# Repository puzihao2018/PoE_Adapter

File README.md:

# PoE_Adapter

## The Idea

## Requirements

* Support 802.3af, at, bt
* Maximum PoE input 71W
* Support 10M/100M/1G Ethernet, 2.5G or 10G better
* Support USB PD 60W(20V-3A) or higher, max to 65W
* Support USB PD 2.0 or higher, PPS support is better

## Related Knowledge

### About PoE

[什么是Power over Ethernet（PoE）? 它是如何工作的？ - 华为](https://info.support.huawei.com/info-finder/encyclopedia/zh/PoE.html)

[Power over Ethernet - Wikipedia](https://en.wikipedia.org/wiki/Power_over_Ethernet)

[【全系列】电源大咖课终极篇：EMC/功率隔离/PoE/LTspice_哔哩哔哩_bilibili](https://www.bilibili.com/video/BV1U54y167iA?p=6&vd_source=4a5614e8aaa017dad2b9a475db5972fe)

### About DCDC

### About USB2ETH

## Key Components

* [ ] 网口变压器
* [ ] PoE Interface IC
* [ ] ETH PHY Chip, MDI/MDIX to SGMII
* [ ] DCDC
* [ ] PD Control IC
* [ ] USB2ETH IC

## Possible Test Equipments

### PSE Devices

[HUAWEI ****AD-560161T0E POE++ Injector****](https://www.notion.so/HUAWEI-AD-560161T0E-POE-Injector-f2f963361bf641c6bf67e5bd52b6a7db)

[**Cudy POE400 90W Gigabit Ultra PoE++ Injector Adapter**](https://www.notion.so/Cudy-POE400-90W-Gigabit-Ultra-PoE-Injector-Adapter-ba70eb35d22a4e3bbaf1a9ec274cac1c)

[H3C S5130S-10MS-UPWR-EI Switch](https://www.notion.so/H3C-S5130S-10MS-UPWR-EI-Switch-632d7c23edca47faa28a7068c8aec5ac)

[QNAP ****QSW-M2116P-2T2S Switch****](https://www.notion.so/QNAP-QSW-M2116P-2T2S-Switch-efeddbc0777d48369dd353b2ddde7140)

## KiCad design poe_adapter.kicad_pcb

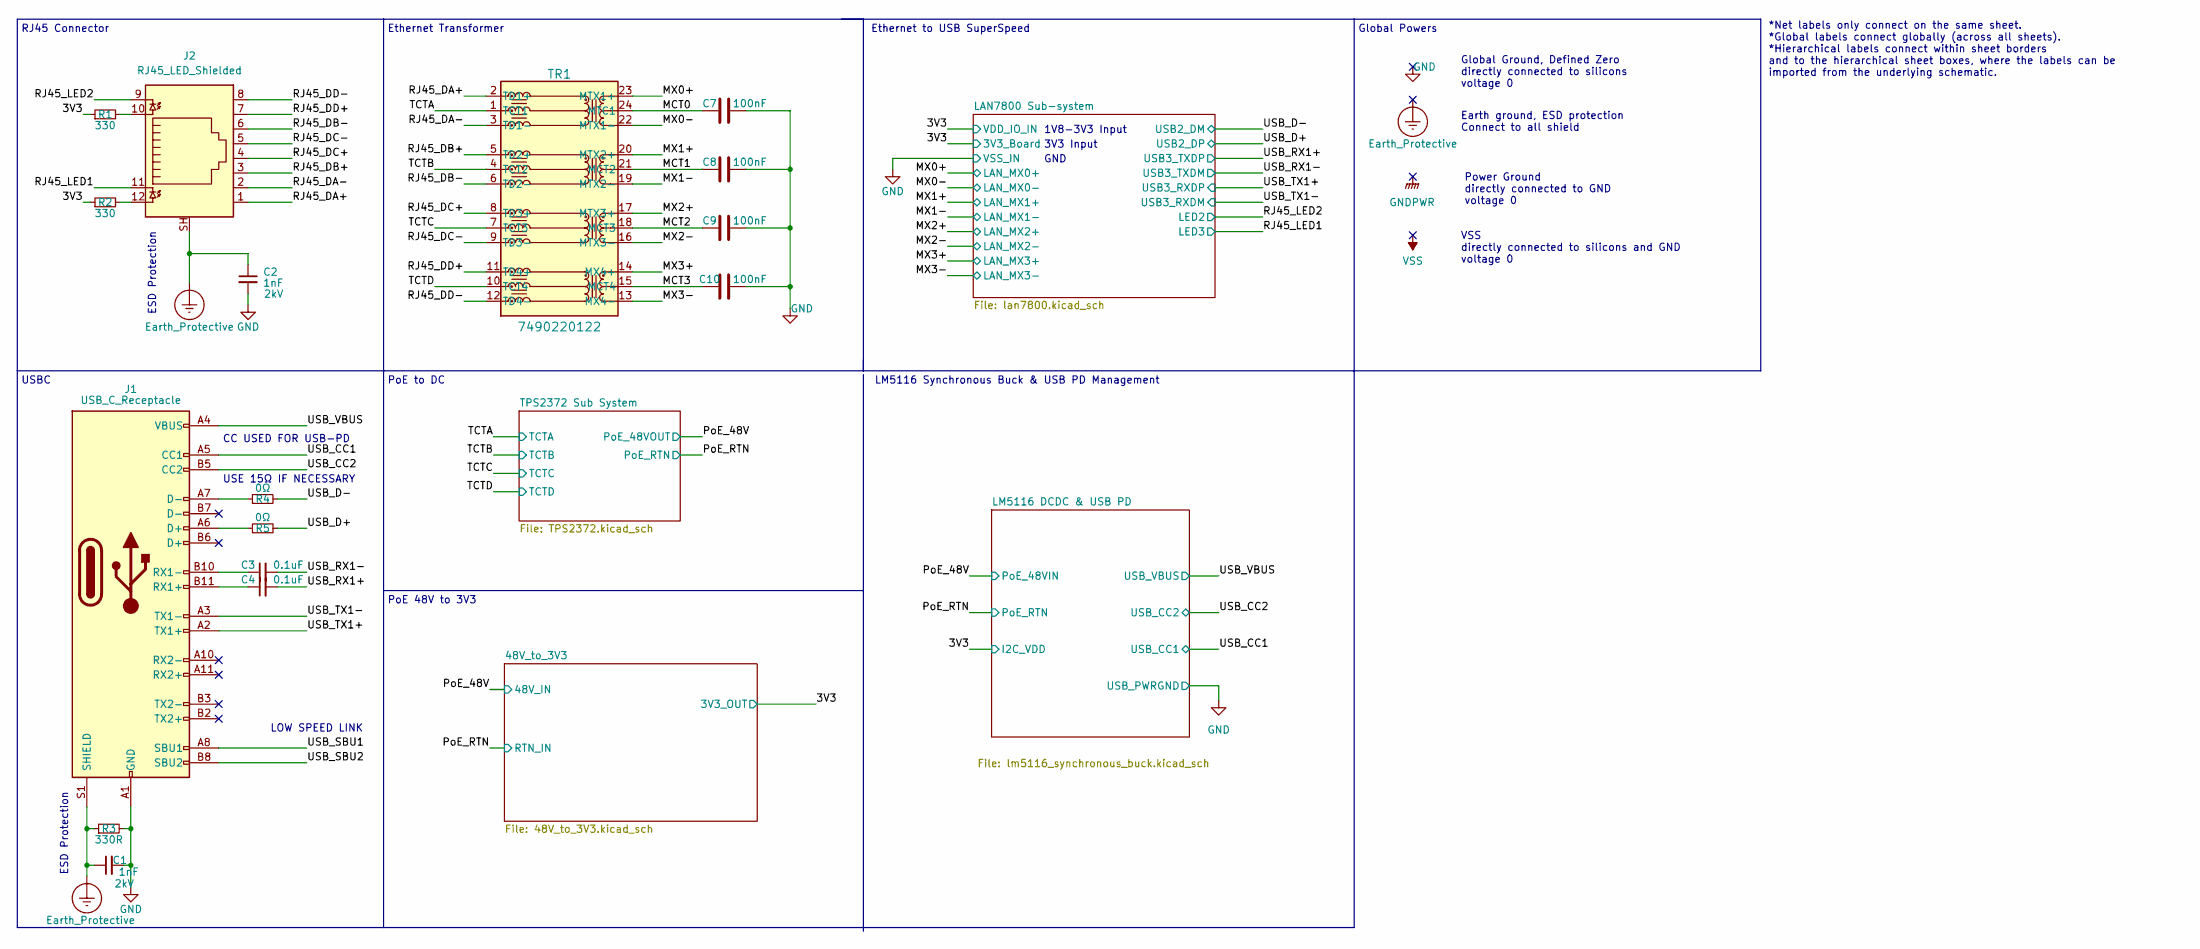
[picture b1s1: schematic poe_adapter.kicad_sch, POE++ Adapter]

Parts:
C1: 1nF; C_1206_3216Metric; Voltage 2kV
C2: 1nF; R_1206_3216Metric; Voltage 2kV
C3, C4: 0.1uF; C_0603_1608Metric
C7, C8, C9, C10: 100nF; C_1206_3216Metric
J1: USB_C_Receptacle; USB_C_Receptacle_Amphenol_12401610E4-2A_CircularHoles
J2: RJ45_LED_Shielded; RJ45_Amphenol_RJHSE538X
R1, R2: 330; R_0603_1608Metric
R3: 330R; R_0603_1608Metric
R4, R5: 0Ω; R_0603_1608Metric
TR1: 7490220122

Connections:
/MCT0: C7.2, TR1.24 (MTC1)
/MCT1: C8.2, TR1.21 (MCT2)
/MCT2: C9.2, TR1.18 (MCT3)
/MCT3: C10.2, TR1.15 (MCT4)
/MX0+: TR1.23 (MTX1+); also elsewhere on the board
/MX0-: TR1.22 (MTX1-); also elsewhere on the board
/MX1+: TR1.20 (MTX2+); also elsewhere on the board
/MX1-: TR1.19 (MTX2-); also elsewhere on the board
/MX2+: TR1.17 (MTX3+); also elsewhere on the board
/MX2-: TR1.16 (MTX3-); also elsewhere on the board
/MX3+: TR1.14 (MX4+); also elsewhere on the board
/MX3-: TR1.13 (MX4-); also elsewhere on the board
/RJ45_DA+: J2.1, TR1.2 (TD1+)
/RJ45_DA-: J2.2, TR1.3 (TD1-)
/RJ45_DB+: J2.3, TR1.5 (TD2+)
/RJ45_DB-: J2.6, TR1.6 (TD2-)
/RJ45_DC+: J2.4, TR1.8 (TD3+)
/RJ45_DC-: J2.5, TR1.9 (TD3-)
/RJ45_DD+: J2.7, TR1.11 (TD4+)
/RJ45_DD-: J2.8, TR1.12 (TD4-)
/RJ45_LED1: J2.11; also elsewhere on the board
/RJ45_LED2: J2.9; also elsewhere on the board
/TCTA: TR1.1 (TCT1); also elsewhere on the board
/TCTB: TR1.4 (TCT2); also elsewhere on the board
/TCTC: TR1.7 (TCT3); also elsewhere on the board
/TCTD: TR1.10 (TCT4); also elsewhere on the board
/USB_CC1: J1.A5 (CC1); also elsewhere on the board
/USB_CC2: J1.B5 (CC2); also elsewhere on the board
/USB_D+: R5.2; also elsewhere on the board
/USB_D-: R4.2; also elsewhere on the board
/USB_RX1+: C4.2; also elsewhere on the board
/USB_RX1-: C3.2; also elsewhere on the board
/USB_SBU1: J1.A8 (SBU1)
/USB_SBU2: J1.B8 (SBU2)
/USB_TX1+: J1.A2 (TX1+); also elsewhere on the board
/USB_TX1-: J1.A3 (TX1-); also elsewhere on the board
/USB_VBUS: J1.A4 (VBUS), J1.A9 (VBUS), J1.B4 (VBUS), J1.B9 (VBUS); also elsewhere on the board
Earth_Protective: C1.1, C2.1, J1.S1 (SHIELD), J2.SH, R3.1; also elsewhere on the board
unnamed: C3.1, J1.B10 (RX1-)
unnamed: C4.1, J1.B11 (RX1+)
unnamed: J1.A6 (D+), R5.1
unnamed: J1.A7 (D-), R4.1
unnamed: J2.10, R1.2
unnamed: J2.12, R2.2

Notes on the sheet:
USE 15Ω IF NECESSARY
RJ45 Connector
1V8-3V3 Input
Ethernet to USB SuperSpeed
Ethernet Transformer
PoE to DC
Earth ground, ESD protection Connect to all shield
Global Ground, Defined Zero directly connected to silicons voltage 0
USBC
GND
3V3 Input
CC USED FOR USB-PD
ESD Protection
LOW SPEED LINK
Power Ground directly connected to GND voltage 0
*Net labels only connect on the same sheet. *Global labels connect globally (across all sheets). *Hierarchical labels connect within sheet borders and to the hierarchical sheet boxes, where the labels can be imported from the underlying schematic.
VSS directly connected to silicons and GND voltage 0
PoE 48V to 3V3
LM5116 Synchronous Buck & USB PD Management
Global Powers

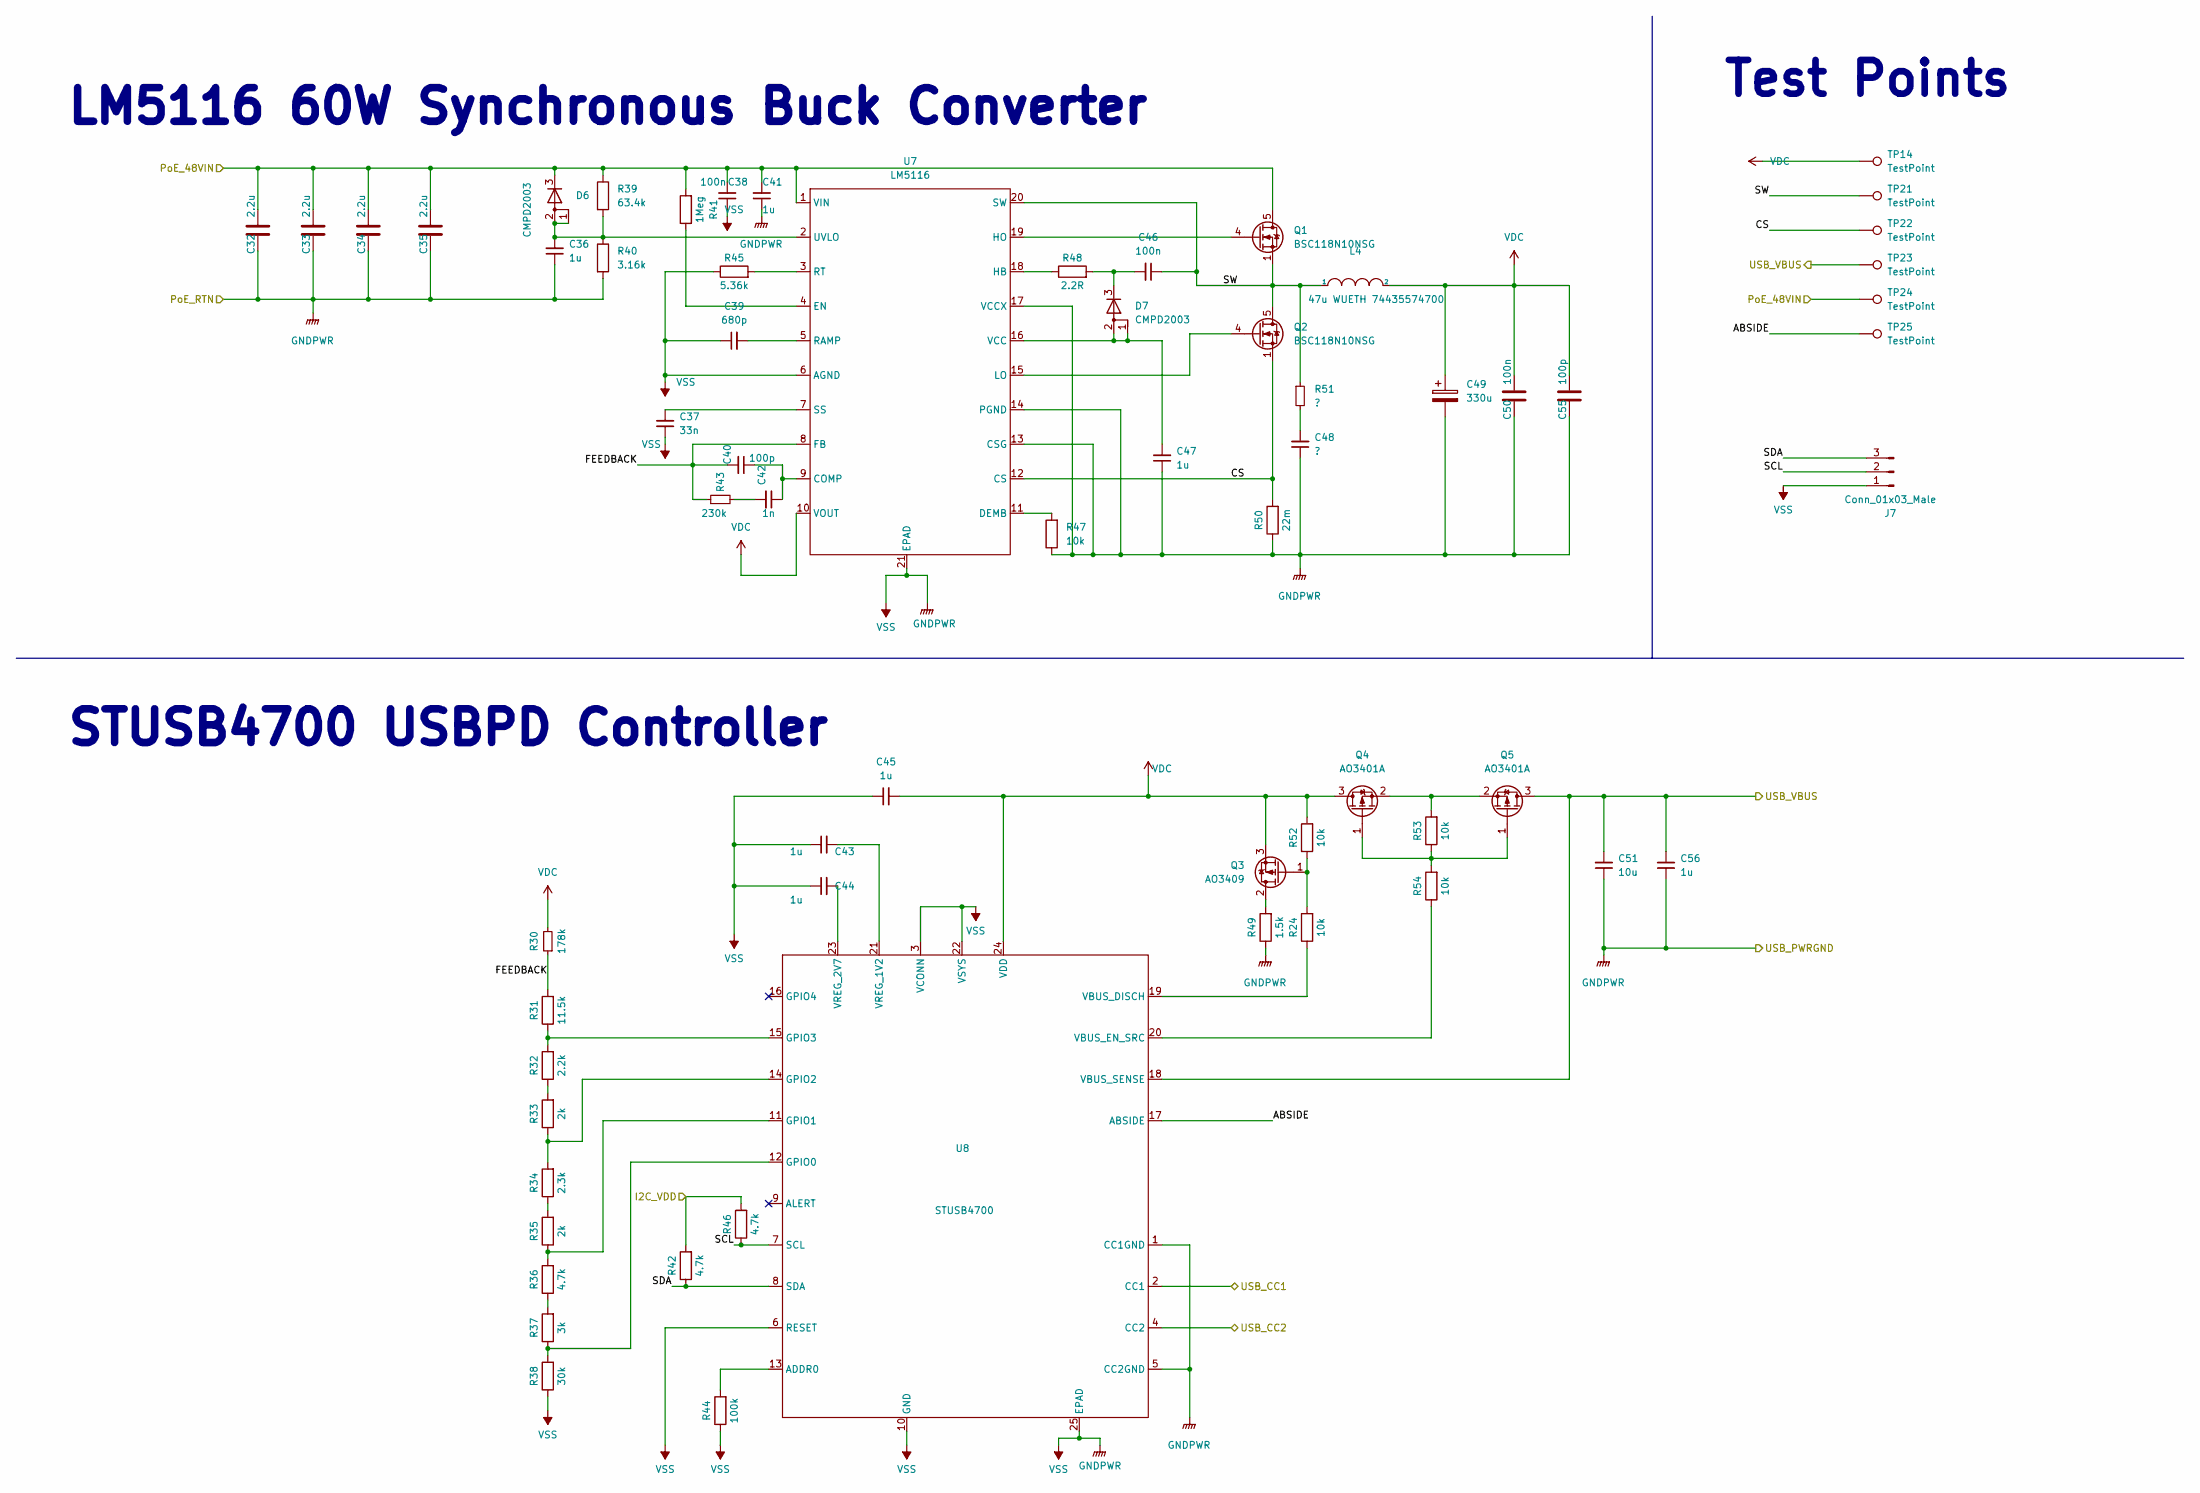
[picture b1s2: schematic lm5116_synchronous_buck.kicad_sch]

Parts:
C32, C33, C34, C35: 2.2u; C_0603_1608Metric
C36, C41, C43, C44, C45, C47, C56: 1u; C_0603_1608Metric
C37: 33n; C_0603_1608Metric
C38, C46, C50: 100n; C_0603_1608Metric
C39: 680p; C_0603_1608Metric
C40, C55: 100p; C_0603_1608Metric
C42: 1n; C_0603_1608Metric
C48: ?; C_0603_1608Metric
C49: 330u; C_Elec_10x10.2
C51: 10u; C_0805_2012Metric
D6, D7: CMPD2003; SOT-23
J7: Conn_01x03_Male; PinHeader_1x03_P1.00mm_Vertical
L4: 47u WUETH 74435574700; 74435574700
Q1, Q2: BSC118N10NSG; TDSON-8-1
Q3: AO3409; SOT-23
Q4, Q5: AO3401A; SOT-23
R24, R47, R52, R53, R54: 10k; R_0603_1608Metric
R30: 178k; R_0603_1608Metric
R31: 11.5k; R_0603_1608Metric
R32: 2.2k; R_0603_1608Metric
R33, R35: 2k; R_0603_1608Metric
R34: 2.3k; R_0603_1608Metric
R36, R42, R46: 4.7k; R_0603_1608Metric
R37: 3k; R_0603_1608Metric
R38: 30k; R_0603_1608Metric
R39: 63.4k; R_0603_1608Metric
R40: 3.16k; R_0603_1608Metric
R41: 1Meg; R_0603_1608Metric
R43: 230k; R_0603_1608Metric
R44: 100k; R_0603_1608Metric
R45: 5.36k; R_0603_1608Metric
R48: 2.2R; R_0805_2012Metric
R49: 1.5k; R_0603_1608Metric
R50: 22m; R_1206_3216Metric
R51: ?; R_0603_1608Metric
TP14, TP21, TP22, TP23, TP24, TP25: TestPoint; TestPoint_Pad_1.0x1.0mm
U7: LM5116; HTSSOP-20-1EP_4.4x6.5mm_P0.65mm_EP2.85x4mm
U8: STUSB4700; QFN-24-1EP_4x4mm_P0.5mm_EP2.7x2.7mm_ThermalVias

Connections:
/LM5116 DCDC & USB PD/ABSIDE: TP25.1, U8.17 (ABSIDE)
/LM5116 DCDC & USB PD/CS: Q2.1 (S), Q2.2 (S), Q2.3 (S), R50.2, TP22.1, U7.12 (CS)
/LM5116 DCDC & USB PD/FEEDBACK: C40.2, R30.1, R31.2, R43.1, U7.8 (FB)
/LM5116 DCDC & USB PD/SCL: J7.2, R46.1, U8.7 (SCL)
/LM5116 DCDC & USB PD/SDA: J7.3, R42.1, U8.8 (SDA)
/LM5116 DCDC & USB PD/SW: C46.1, L4.1, Q1.1 (S), Q1.2 (S), Q1.3 (S), Q2.5 (D), R51.1, TP21.1, U7.20 (SW)
/PoE_48V: C32.1, C33.1, C34.1, C35.1, C38.2, C41.2, D6.3 (K), Q1.5 (D), R39.1, R41.2, TP24.1, U7.1 (VIN); also elsewhere on the board
/USB_CC1: U8.2 (CC1); also elsewhere on the board
/USB_CC2: U8.4 (CC2); also elsewhere on the board
/USB_VBUS: C51.2, C56.2, Q5.3 (D), TP23.1, U8.18 (VBUS_SENSE); also elsewhere on the board
unnamed: C36.2, D6.1 (A), D6.2 (A), R39.2, R40.1, U7.2 (UVLO)
unnamed: C37.2, U7.7 (SS)
unnamed: C39.2, U7.5 (RAMP)
unnamed: C40.1, C42.1, U7.9 (COMP)
unnamed: C42.2, R43.2
unnamed: C43.2, U8.21 (VREG_1V2)
unnamed: C44.2, U8.23 (VREG_2V7)
unnamed: C46.2, D7.3 (K), R48.2
unnamed: C47.2, D7.1 (A), D7.2 (A), U7.16 (VCC)
unnamed: C48.2, R51.2
unnamed: Q1.4 (G), U7.19 (HO)
unnamed: Q2.4 (G), U7.15 (LO)
unnamed: Q3.1 (G), R24.2, R52.1
unnamed: Q3.2 (D), R49.2
unnamed: Q4.1 (G), Q5.1 (G), R53.1, R54.2
unnamed: Q4.2 (S), Q5.2 (S), R53.2
unnamed: R24.1, U8.19 (VBUS_DISCH)
unnamed: R31.1, R32.2, U8.15 (GPIO3)
unnamed: R32.1, R33.2
unnamed: R33.1, R34.2, U8.14 (GPIO2)
unnamed: R34.1, R35.2
unnamed: R35.1, R36.2, U8.11 (GPIO1)
unnamed: R36.1, R37.2
unnamed: R37.1, R38.2, U8.12 (GPIO0)
unnamed: R41.1, U7.4 (EN)
unnamed: R44.2, U8.13 (ADDR0)
unnamed: R45.2, U7.3 (RT)
unnamed: R47.2, U7.11 (DEMB)
unnamed: R48.1, U7.18 (HB)
unnamed: R54.1, U8.20 (VBUS_EN_SRC)
VDC: C45.2, C49.1, C50.1, C55.1, L4.2, Q3.3 (S), Q4.3 (D), R30.2, R52.2, TP14.1, U7.10 (VOUT), U8.24 (VDD)

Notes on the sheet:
STUSB4700 USBPD Controller
Test Points
LM5116 60W Synchronous Buck Converter

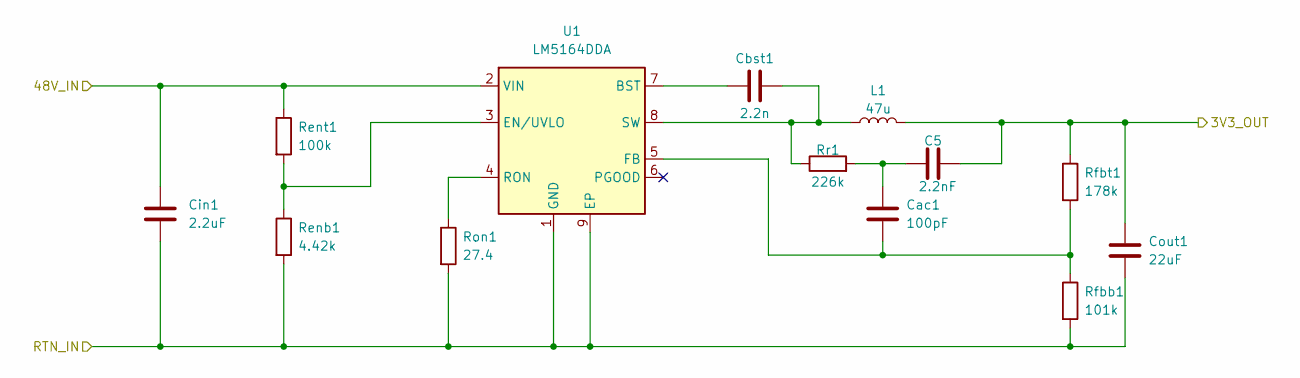
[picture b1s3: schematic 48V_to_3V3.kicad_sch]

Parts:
C5: 2.2nF; C_0603_1608Metric
Cac1: 100pF; C_0603_1608Metric
Cbst1: 2.2n; C_0603_1608Metric
Cin1: 2.2uF; C_1206_3216Metric
Cout1: 22uF; C_1206_3216Metric
L1: 47u; L_Wuerth_HCI-5040
Renb1: 4.42k; R_0603_1608Metric
Rent1: 100k; R_0603_1608Metric
Rfbb1: 101k; R_0603_1608Metric
Rfbt1: 178k; R_0603_1608Metric
Ron1: 27.4; R_0603_1608Metric
Rr1: 226k; R_0603_1608Metric
U1: LM5164DDA; HSOP-8-1EP_3.9x4.9mm_P1.27mm_EP2.41x3.1mm_ThermalVias

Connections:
/PoE_48V: C5.1, Cac1.2, Cin1.2, Cout1.1, Renb1.2, Rfbb1.2, Ron1.2, Rr1.2, U1.1 (VIN), U1.9 (EP); also elsewhere on the board
unnamed: Cbst1.1, U1.7 (BST)
unnamed 96: Ron1.1, U1.4 (FB); also elsewhere on the board

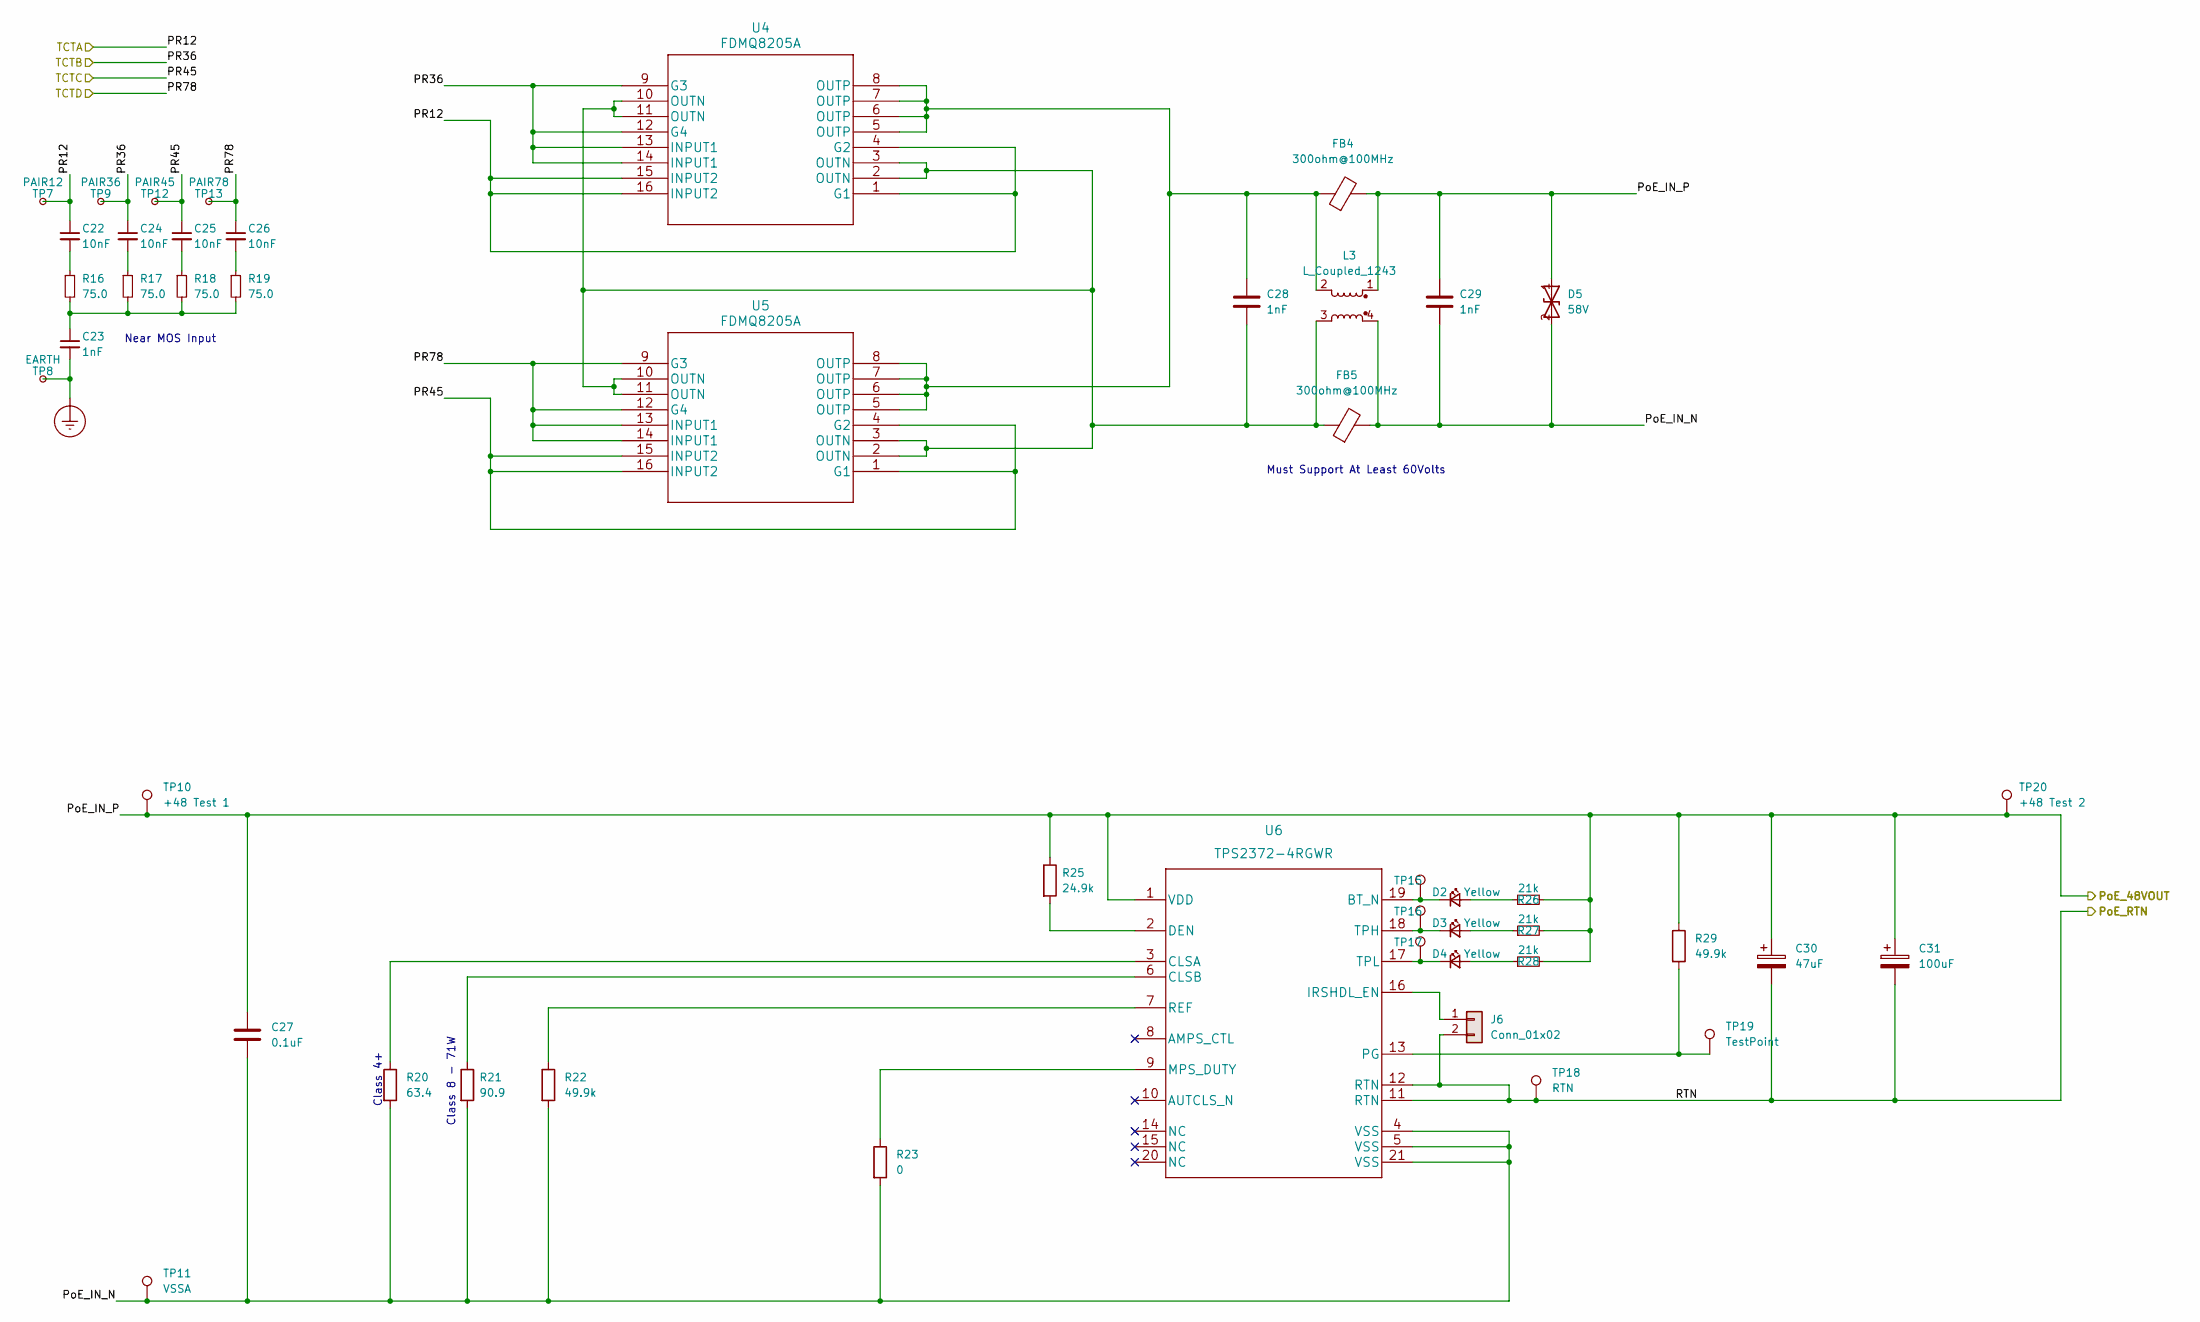
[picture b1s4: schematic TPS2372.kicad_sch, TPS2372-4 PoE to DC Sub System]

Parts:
C22, C24, C25, C26: 10nF; C_0603_1608Metric
C23, C28, C29: 1nF; C_0603_1608Metric
C27: 0.1uF; C_0805_2012Metric
C30: 47uF; EEV-TG2A470Q
C31: 100uF; CP_Elec_16x17.5
D2, D3, D4: Yellow; D_0603_1608Metric
D5: 58V; D_SMB
FB4, FB5: 300ohm@100MHz; L_0603_1608Metric
J6: Conn_01x02; PinHeader_1x02_P2.54mm_Vertical
L3: L_Coupled_1243; 744272251
R16, R17, R18, R19: 75.0; R_0603_1608Metric
R20: 63.4; R_0201_0603Metric
R21: 90.9; R_0603_1608Metric
R22, R29: 49.9k; R_0603_1608Metric
R23: 0; R_0603_1608Metric
R25: 24.9k; R_0603_1608Metric
R26, R27, R28: 21k; R_0603_1608Metric
TP7: PAIR12; TestPoint_Pad_1.0x1.0mm
TP8: EARTH; TestPoint_Pad_1.0x1.0mm
TP9: PAIR36; TestPoint_Pad_1.0x1.0mm
TP10: +48 Test 1; TestPoint_Pad_1.0x1.0mm
TP11: VSSA; TestPoint_Pad_1.0x1.0mm
TP12: PAIR45; TestPoint_Pad_1.0x1.0mm
TP13: PAIR78; TestPoint_Pad_1.0x1.0mm
TP15, TP16, TP17, TP19: TestPoint; TestPoint_Pad_1.0x1.0mm
TP18: RTN; TestPoint_Pad_1.0x1.0mm
TP20: +48 Test 2; TestPoint_Pad_1.0x1.0mm
U4, U5: FDMQ8205A
U6: TPS2372-4RGWR; TPS2372-3RGWR

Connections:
/PoE_48V: C27.1, C29.1, C30.1, C31.1, D5.1 (A1), FB4.2, L3.1, R25.1, R26.2, R27.2, R28.2, R29.1, TP10.1, TP20.1, U6.1 (VDD); also elsewhere on the board
/TCTA: C22.1, TP7.1, U4.1 (G1), U4.4 (G2), U4.15 (INPUT2), U4.16 (INPUT2); also elsewhere on the board
/TCTB: C24.1, TP9.1, U4.9 (G3), U4.12 (G4), U4.13 (INPUT1), U4.14 (INPUT1); also elsewhere on the board
/TCTC: C25.1, TP12.1, U5.1 (G1), U5.4 (G2), U5.15 (INPUT2), U5.16 (INPUT2); also elsewhere on the board
/TCTD: C26.1, TP13.1, U5.9 (G3), U5.12 (G4), U5.13 (INPUT1), U5.14 (INPUT1); also elsewhere on the board
/TPS2372 Sub System/PoE_IN_N: C27.2, C29.2, D5.2 (A2), FB5.2, L3.4, R20.2, R21.2, R22.2, R23.2, TP11.1, U6.4 (VSS), U6.5 (VSS), U6.21 (VSS)
Earth_Protective: C23.2, TP8.1; also elsewhere on the board
unnamed: C22.2, R16.1
unnamed: C23.1, R16.2, R17.2, R18.2, R19.2
unnamed: C24.2, R17.1
unnamed: C25.2, R18.1
unnamed: C26.2, R19.1
unnamed: C28.1, FB4.1, L3.2, U4.5 (OUTP), U4.6 (OUTP), U4.7 (OUTP), U4.8 (OUTP), U5.5 (OUTP), U5.6 (OUTP), U5.7 (OUTP), U5.8 (OUTP)
unnamed: C28.2, FB5.1, L3.3, U4.2 (OUTN), U4.3 (OUTN), U4.10 (OUTN), U4.11 (OUTN), U5.2 (OUTN), U5.3 (OUTN), U5.10 (OUTN), U5.11 (OUTN)
unnamed: D2.1 (K), TP15.1, U6.19 (BT_N)
unnamed: D2.2 (A), R26.1
unnamed: D3.1 (K), TP16.1, U6.18 (TPH)
unnamed: D3.2 (A), R27.1
unnamed: D4.1 (K), TP17.1, U6.17 (TPL)
unnamed: D4.2 (A), R28.1
unnamed: J6.1, U6.16 (IRSHDL_EN)
unnamed: R20.1, U6.3 (CLSA)
unnamed: R21.1, U6.6 (CLSB)
unnamed: R22.1, U6.7 (REF)
unnamed: R23.1, U6.9 (MPS_DUTY)
unnamed: R25.2, U6.2 (DEN)
unnamed: R29.2, TP19.1, U6.13 (PG)

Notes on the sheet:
Class 8 - 71W
Near MOS Input
Class 4+
Must Support At Least 60Volts

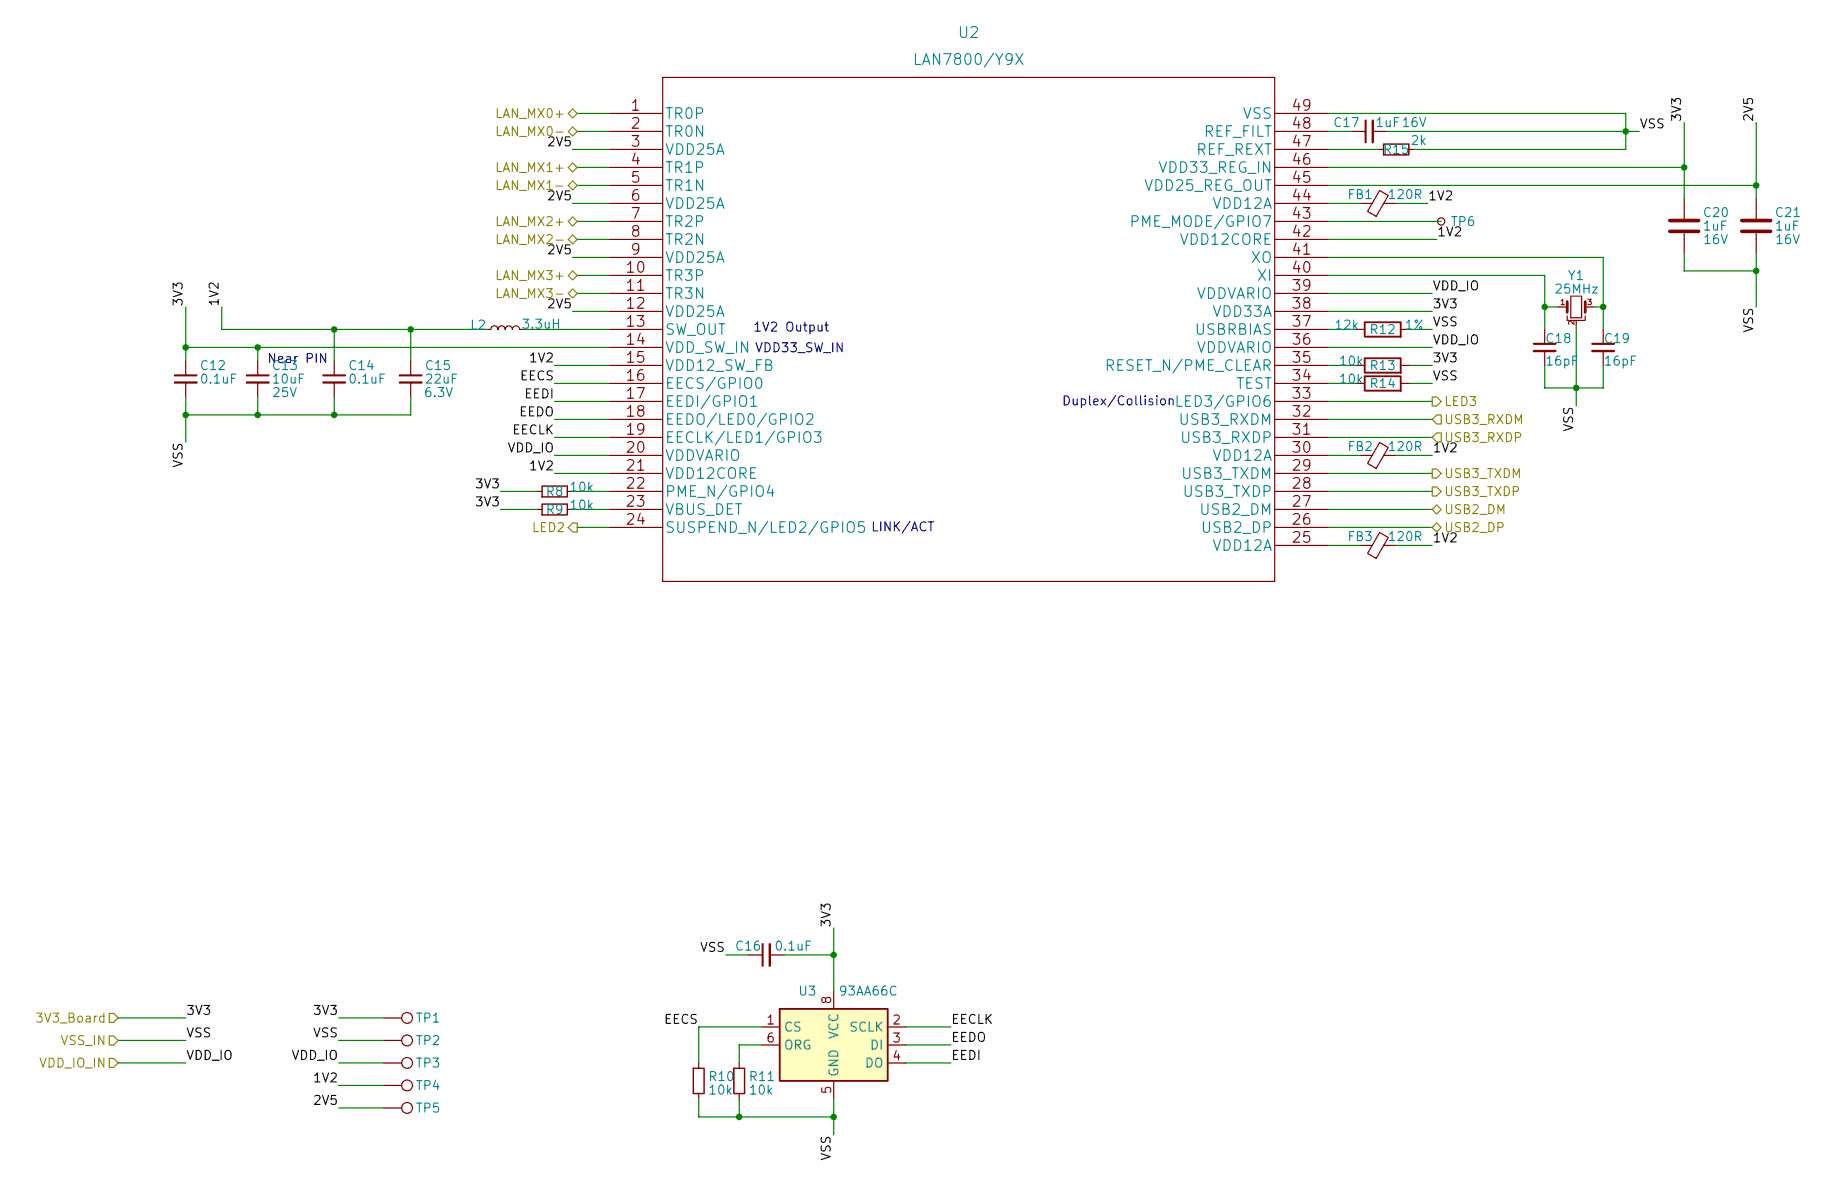
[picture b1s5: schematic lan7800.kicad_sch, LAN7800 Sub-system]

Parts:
C12, C14, C16: 0.1uF; C_0603_1608Metric
C13: 10uF; C_0603_1608Metric; Voltage 25V
C15: 22uF; C_0603_1608Metric; Voltage 6.3V
C17, C20, C21: 1uF; C_0603_1608Metric; Voltage 16V
C18, C19: 16pF; C_0603_1608Metric
FB1: 120R; L_0603_1608Metric
FB2, FB3: 120R; R_0603_1608Metric
L2: 3.3uH; L_1206_3216Metric
R8, R9, R10, R11, R13, R14: 10k; R_0603_1608Metric
R12: 12k; R_0603_1608Metric
R15: 2k; R_0603_1608Metric
TP1, TP2, TP3, TP4, TP5: TestPoint; TestPoint_Pad_1.0x1.0mm
TP6: TestPoint_Small; TestPoint_Pad_1.0x1.0mm
U2: LAN7800/Y9X; LAN7800&slash_Y9X
U3: 93AA66C; SOIC-8-1EP_3.9x4.9mm_P1.27mm_EP2.29x3mm
Y1: 25MHz; Crystal_SMD_3225-4Pin_3.2x2.5mm

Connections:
/LAN7800 Sub-system/1V2: C14.1, C15.1, FB1.2, FB2.2, FB3.2, L2.1, TP4.1, U2.15 (VDD12_SW_FB), U2.21 (VDD12CORE), U2.42 (VDD12CORE)
/LAN7800 Sub-system/2V5: C21.1, TP5.1, U2.3 (VDD25A), U2.6 (VDD25A), U2.9 (VDD25A), U2.12 (VDD25A), U2.45 (VDD25_REG_OUT)
/LAN7800 Sub-system/EECLK: U2.19 (EECLK/LED1/GPIO3), U3.2 (SCLK)
/LAN7800 Sub-system/EECS: R10.1, U2.16 (EECS/GPIO0), U3.1 (CS)
/LAN7800 Sub-system/EEDI: U2.17 (EEDI/GPIO1), U3.4 (DO)
/LAN7800 Sub-system/EEDO: U2.18 (EEDO/LED0/GPIO2), U3.3 (DI)
/MX0+: U2.1 (TR0P); also elsewhere on the board
/MX0-: U2.2 (TR0N); also elsewhere on the board
/MX1+: U2.4 (TR1P); also elsewhere on the board
/MX1-: U2.5 (TR1N); also elsewhere on the board
/MX2+: U2.7 (TR2P); also elsewhere on the board
/MX2-: U2.8 (TR2N); also elsewhere on the board
/MX3+: U2.10 (TR3P); also elsewhere on the board
/MX3-: U2.11 (TR3N); also elsewhere on the board
/RJ45_LED1: U2.33 (LED3/GPIO6); also elsewhere on the board
/RJ45_LED2: U2.24 (SUSPEND_N/LED2/GPIO5); also elsewhere on the board
/USB_D+: U2.26 (USB2_DP); also elsewhere on the board
/USB_D-: U2.27 (USB2_DM); also elsewhere on the board
/USB_RX1+: U2.28 (USB3_TXDP); also elsewhere on the board
/USB_RX1-: U2.29 (USB3_TXDM); also elsewhere on the board
/USB_TX1+: U2.31 (USB3_RXDP); also elsewhere on the board
/USB_TX1-: U2.32 (USB3_RXDM); also elsewhere on the board
unnamed: C17.1, U2.48 (REF_FILT)
unnamed: C18.1, U2.40 (XI), Y1.1
unnamed: C19.1, U2.41 (XO), Y1.3
unnamed: FB1.1, U2.44 (VDD12A)
unnamed: FB2.1, U2.30 (VDD12A)
unnamed: FB3.1, U2.25 (VDD12A)
unnamed: L2.2, U2.13 (SW_OUT)
unnamed: R8.2, U2.22 (PME_N/GPIO4)
unnamed: R9.2, U2.23 (VBUS_DET)
unnamed: R11.1, U3.6 (ORG)
unnamed: R12.1, U2.37 (USBRBIAS)
unnamed: R13.1, U2.35 (RESET_N/PME_CLEAR)
unnamed: R14.1, U2.34 (TEST)
unnamed: R15.1, U2.47 (REF_REXT)
unnamed: TP6.1, U2.43 (PME_MODE/GPIO7)

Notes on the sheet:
LINK/ACT
VDD33_SW_IN
1V2 Output
Duplex/Collision
Near PIN

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
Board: 4 copper layers, 170 parts (0 on the bottom side), 126 nets, no tracks yet.

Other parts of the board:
C6, C52, C53: 4.7uF; C_1206_3216Metric
C11: 330uF; CP_Elec_8x10
C54: 100uF; CP_Elec_10x10
D1: 60V 1A; D_SMA
R6: 3.4k; R_0603_1608Metric
R7: 2k; R_0603_1608Metric

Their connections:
/PoE_48V: C6.1, C52.1, C53.1, C54.1; also elsewhere on the board
unnamed 96: R6.2, R7.1; also elsewhere on the board

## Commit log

2022-07-07 repo init with readme
2022-07-07 LAN7800 Update 220707
2022-07-07 LAN7800 Update 220707-2
2022-07-10 LAN7800 update 0710
2022-07-12 Added initial annotated DCDC ic components and power stage design caculations
2022-07-12 finish datalink
2022-07-12 led update
2022-07-13 *updated power converter design calculations
    *added initial TINA simulation file
2022-07-14 change 20220714, update datalink
2022-07-18 tps2372 init
2022-07-23 changed chip from 2897a to lm5116
2022-07-24 input cap calculation update
2022-07-26 tps2372 finish
2022-07-28 added matlab calculations and phase margin analysis
2022-07-28 new symbol for lm5116
2022-07-28 symble table
2022-07-28 buck converter init
2022-07-28 TPS2372 Modified, test jumpers removed
2022-07-29 PoE TR change to 7490220122; updated pwr net
2022-07-30 LM2575 added, provide 3V3
2022-07-30 * put lm5116 symbol to its own folder
    * added stusb4700 symbol
    * finished DCDC converter schema
2022-07-31 finished schema of lm5116 and USB4700
2022-08-01 added 3v3 for scl & sda pins on stusb4700
2022-08-02 power symbol updated
2022-09-12 finished lm5116 circuit foot print assignment
2022-09-18 PoE Library Update
2022-09-18 footprint for power inductor and cap
2022-09-19 footprint update
2022-09-19 changed CC pin tags
2022-09-20 Footprint without TPS2372
2022-09-21 Footprint done
2022-09-25 ERC Check Finish
2022-09-25 Update PCB
2022-09-25 PCB Design Rule updated
2022-09-25 Layout Update
2022-09-25 crude layout
2022-09-26 Update 3V3 Solution
2022-09-30 layout power stage

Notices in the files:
parts and their libraries:
Copyright 2021 Accelerated Designs. All rights reserved.
